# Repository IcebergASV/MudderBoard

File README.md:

# MudderBoard
KiCad Development of the 2024-2025 PCB; The MudderBoard

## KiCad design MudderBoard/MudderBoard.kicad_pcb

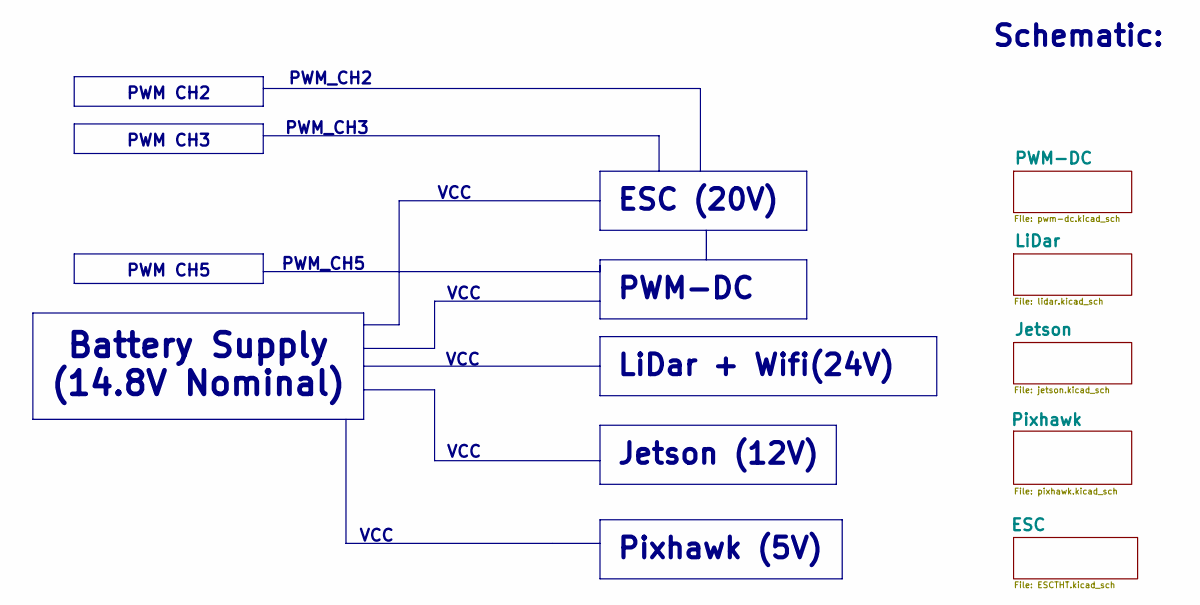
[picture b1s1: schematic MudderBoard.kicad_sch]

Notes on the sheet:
PWM CH2
PWM CH5
Pixhawk (5V)
Jetson (12V)
LiDar + Wifi(24V)
PWM-DC
ESC (20V)
Battery Supply (14.8V Nominal)
PWM CH3
VCC
PWM_CH3
PWM_CH2
PWM_CH5
Schematic:

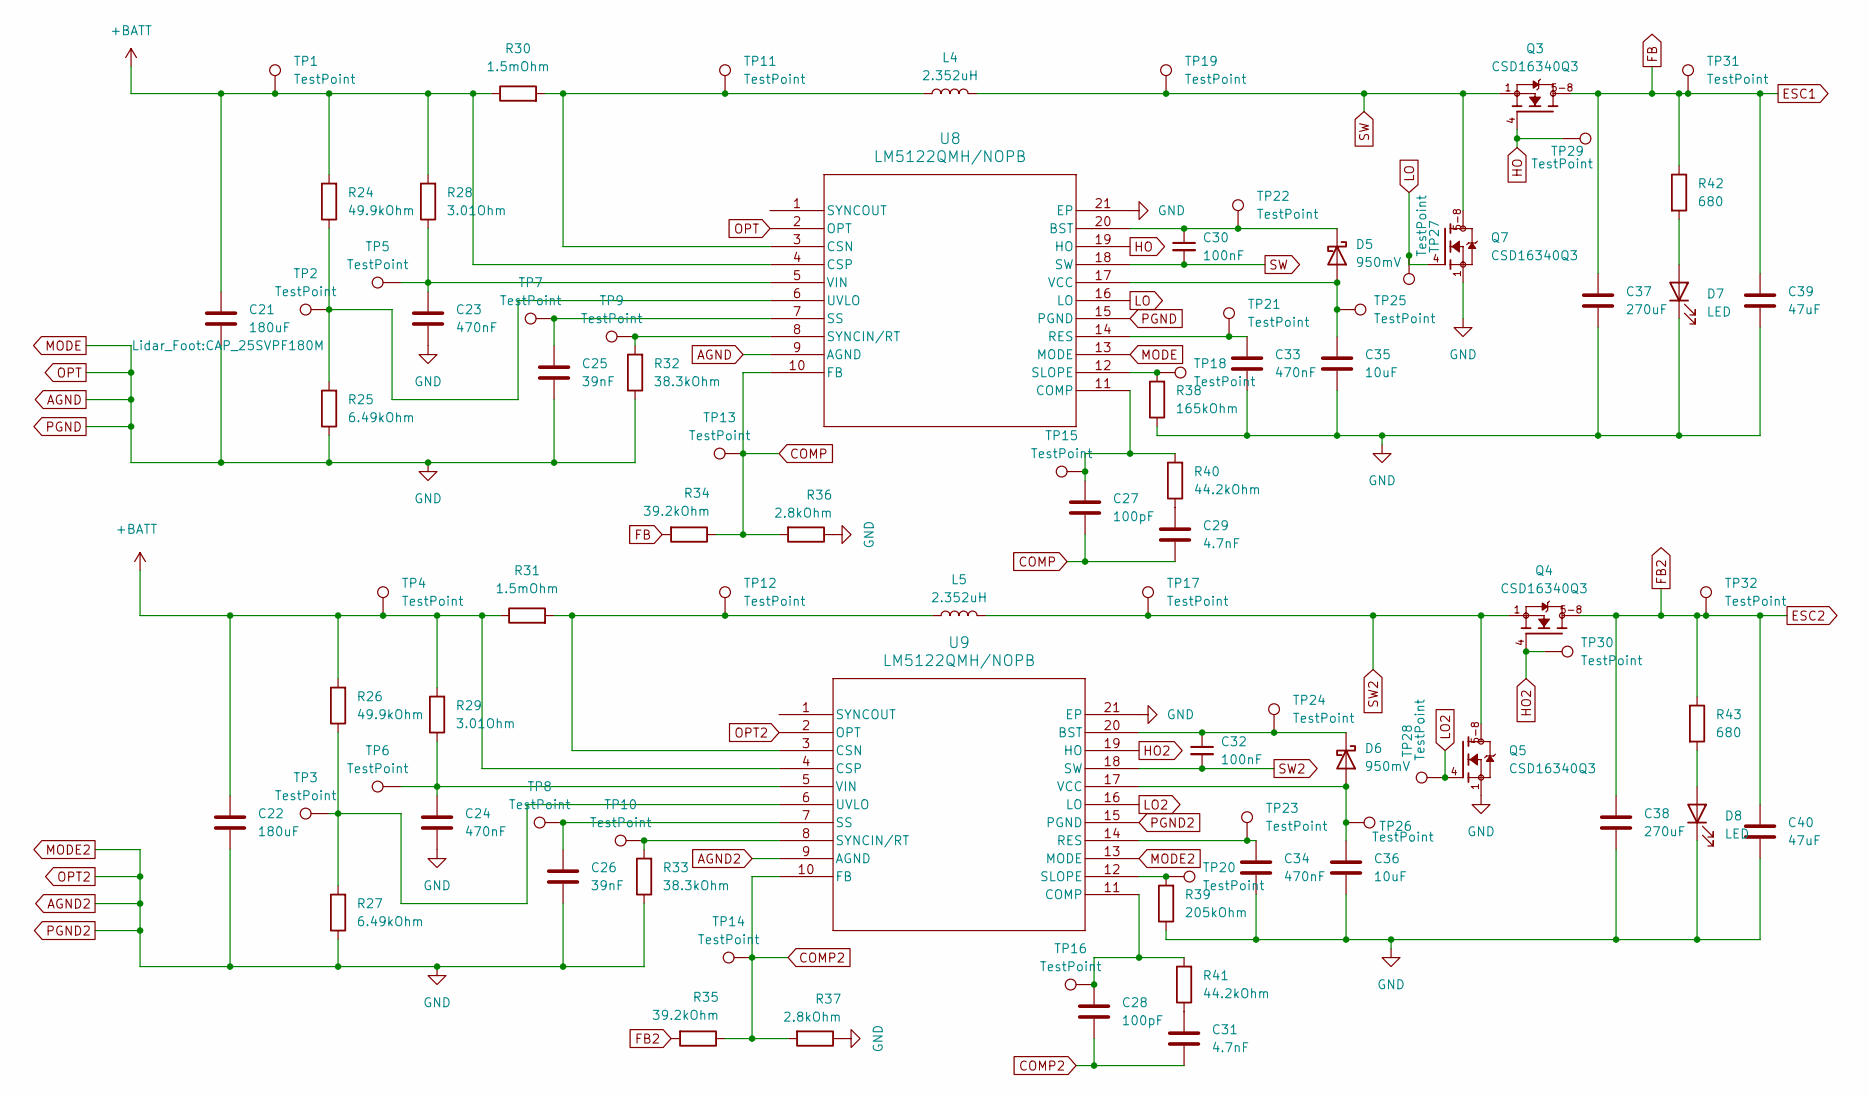
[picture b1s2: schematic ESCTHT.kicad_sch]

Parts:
C21, C22: 180uF; CAP_25SVPF180M
C23, C24: 470nF; CAPC1608X90N
C25, C26: 39nF; CAPC1005X55N
C27, C28: 100pF; CAPC2012X135N
C29, C31: 4.7nF; CAPC2012X75N
C30, C32: 100nF; CAP_CC0805_YAG
C33, C34: 470nF; CAPC2012X95N
C35, C36: 10uF; CAPC2012X135N
C37, C38: 270uF; CAP_EEHZA1V271P
C39, C40: 47uF; CAPC3216X180N
D5, D6: 950mV; CR_DO-214ACSMA_TWS
D7, D8: LED; LED_DRD1204W-TR
L4, L5: 2.352uH; L_Neosid_SM-PIC0512H
Q3, Q4, Q5, Q7: CSD16340Q3; TRANS_CSD16340Q3; PARTREV E
R24, R26: 49.9kOhm; RESC1005X40N
R25, R27: 6.49kOhm; RESC1005X40N
R28, R29: 3.01Ohm; RESC1005X40N
R30, R31: 1.5mOhm; RESC6432X110N
R32, R33: 38.3kOhm; RESC1005X40N
R34, R35: 39.2kOhm; RESC1005X35N
R36, R37: 2.8kOhm; RESC1005X40N
R38: 165kOhm; RESC1005X40N
R39: 205kOhm; RESC1005X40N
R40, R41: 44.2kOhm; RESC0603X28N
R42, R43: 680; RESC3216X70N
TP1, TP2, TP3, TP4, TP5, TP6, TP7, TP8, TP9, TP10, TP11, TP12, TP13, TP14, TP15, TP16, TP17, TP18, TP19, TP20, TP21, TP22, TP23, TP24, TP25, TP26, TP27, TP28, TP29, TP30, TP31, TP32: TestPoint; TestPoint_Keystone_5000-5004_Miniature
U8, U9: LM5122QMH/NOPB; SOP65P640X110-21N

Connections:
+BATT: C21.1, C22.1, R24.2, R26.2, R28.2, R29.2, R30.1, R31.1, TP1.1, TP4.1, U8.4 (CSP), U9.4 (CSP); also elsewhere on the board
AGND: C21.2, C22.2, C23.2, C24.2, C25.2, C26.2, C33.2, C34.2, C35.2, C36.2, C37.2, C38.2, C39.2, C40.2, D7.1 (K), D8.1 (K), Q5.1, Q5.2, Q5.3, Q7.1, R25.1, R27.1, R32.1, R33.1, R36.1, R37.1, R38.1, R39.1, U8.2 (OPT), U8.9 (AGND), U8.13 (MODE), U8.15 (PGND), U8.21 (EP), U9.2 (OPT), U9.9 (AGND), U9.13 (MODE), U9.15 (PGND), U9.21 (EP); also elsewhere on the board
COMP: C27.2, C29.2, R34.1, R36.2, TP13.1, U8.10 (FB)
COMP2: C28.2, C31.2, R35.1, R37.2, TP14.1, U9.10 (FB)
ESC1: C37.1, C39.1, Q3.5-8, R34.2, R42.1, TP31.1
ESC2: C38.1, C40.1, Q4.5-8, R35.2, R43.1, TP32.1
HO: Q3.4, TP29.1, U8.19 (HO)
HO2: Q4.4, TP30.1, U9.19 (HO)
LO: Q7.4, TP27.1, U8.16 (LO)
LO2: Q5.4, TP28.1, U9.16 (LO); also elsewhere on the board
unnamed: C29.1, R40.1
unnamed: C31.1, R41.1
unnamed: C35.1, D5.2 (A), TP25.1, U8.17 (VCC)
unnamed: C30.1, D5.1 (K), TP22.1, U8.20 (BST)
unnamed: C36.1, D6.2 (A), TP26.1, U9.17 (VCC)
unnamed: C32.1, D6.1 (K), TP24.1, U9.20 (BST)
unnamed: D7.2 (A), R42.2
unnamed: D8.2 (A), R43.2
unnamed: C27.1, R40.2, TP15.1, U8.11 (COMP)
unnamed: L4.1, R30.2, TP11.1, U8.3 (CSN)
unnamed: C33.1, TP21.1, U8.14 (RES)
unnamed: R38.2, TP18.1, U8.12 (SLOPE)
unnamed: C25.1, TP7.1, U8.7 (SS)
unnamed: R32.2, TP9.1, U8.8 (SYNCIN/RT)
unnamed: R24.1, R25.2, TP2.1, U8.6 (UVLO)
unnamed: C23.1, R28.1, TP5.1, U8.5 (VIN)
unnamed: C28.1, R41.2, TP16.1, U9.11 (COMP)
unnamed: L5.1, R31.2, TP12.1, U9.3 (CSN)
unnamed: C34.1, TP23.1, U9.14 (RES)
unnamed: R39.2, TP20.1, U9.12 (SLOPE)
unnamed: C26.1, TP8.1, U9.7 (SS)
unnamed: R33.2, TP10.1, U9.8 (SYNCIN/RT)
unnamed: R26.1, R27.2, TP3.1, U9.6 (UVLO)
unnamed: C24.1, R29.1, TP6.1, U9.5 (VIN)
SW: C30.2, L4.2, Q3.1, Q7.5-8, TP19.1, U8.18 (SW)
SW2: C32.2, L5.2, Q4.1, Q4.2, Q4.3, Q5.5-8, TP17.1, U9.18 (SW)

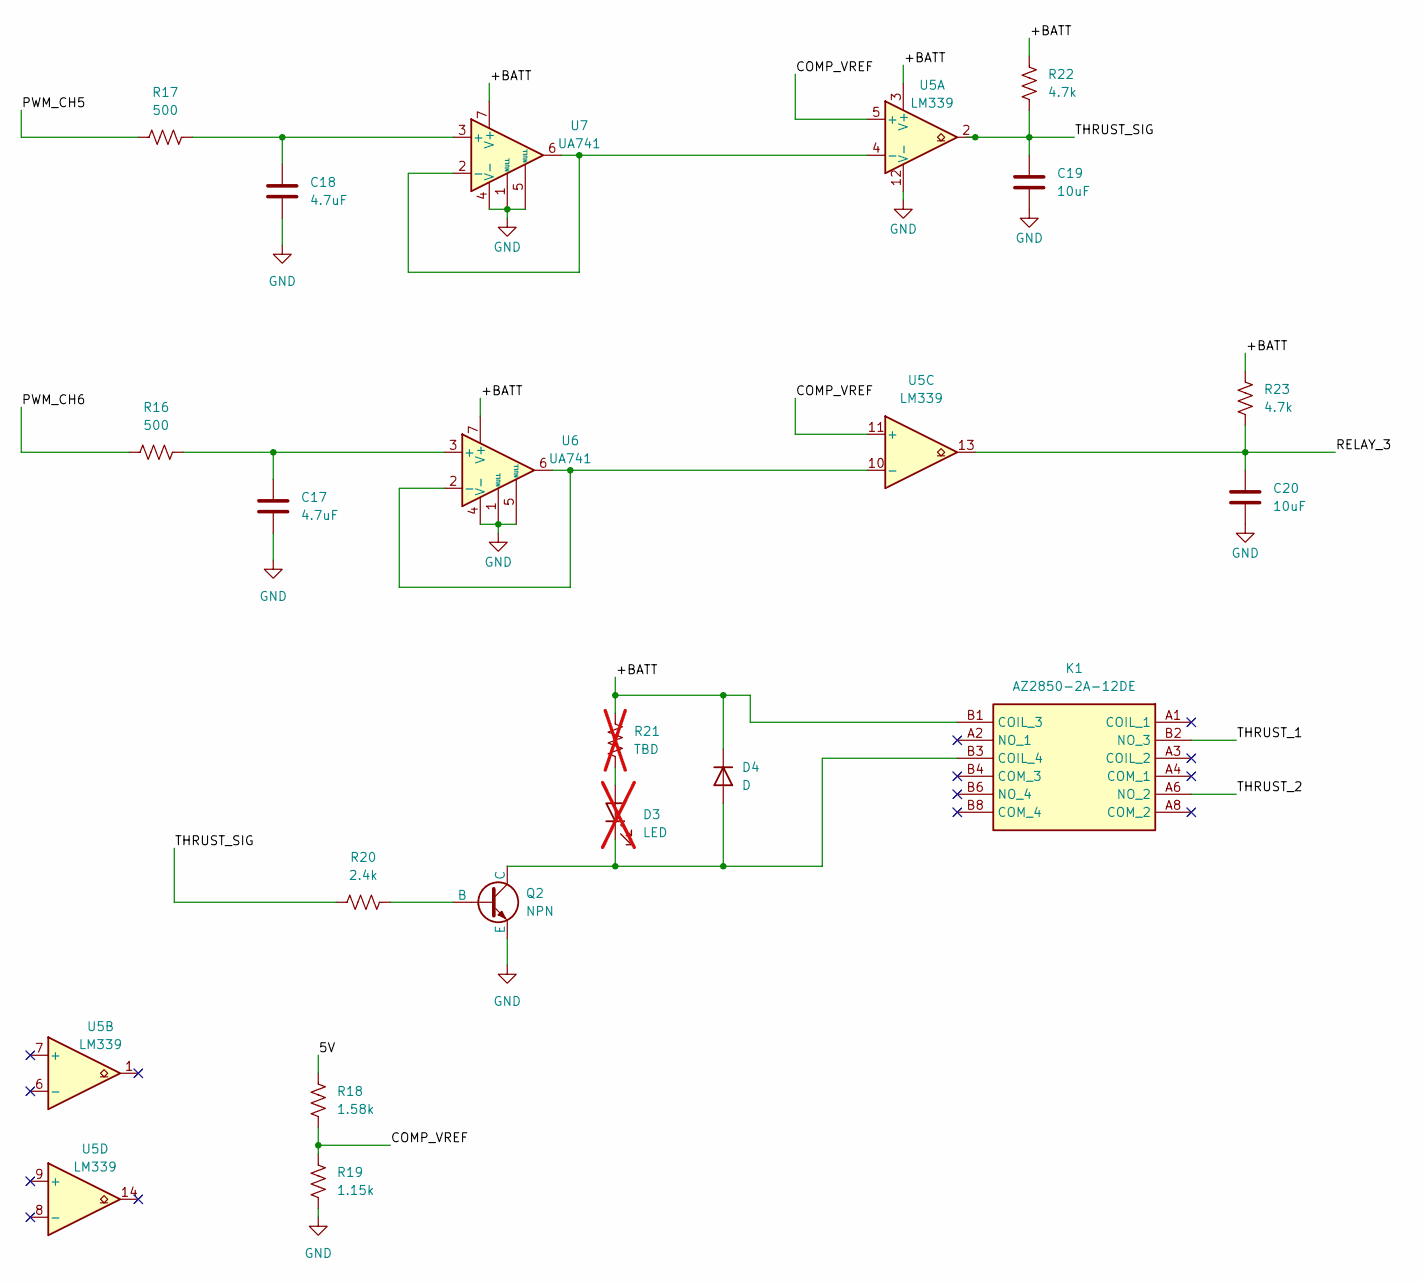
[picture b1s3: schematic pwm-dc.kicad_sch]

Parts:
C17, C18: 4.7uF; CAPC2012X140N
C19, C20: 10uF; CAPC2012X135N
D3: LED; not fitted
D4: D; SOT_45-M3&slash_I_VIS
K1: AZ2850-2A-12DE; AZ28502A12DE; Manufacturer_Part_Number AZ2850-2A-12DE
Q2: NPN; SOT95P237X111-3N
R16, R17: 500; RESC1608X55N
R18: 1.58k; RES_ERA6AEB1581V
R19: 1.15k; RES_ERA6AEB1581V
R20: 2.4k; RESC1607X60N
R21: TBD; not fitted
R22, R23: 4.7k; RESC2012X65N
U5: LM339; TSSOP-14_4.4x5mm_P0.65mm
U6, U7: UA741; SOIC127P599X175-8N

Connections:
/PWM-DC/5V: R18.2
/PWM-DC/+BATT: D4.1 (K), K1.B1 (COIL_3), R21.2, R22.2, R23.2, U5.3 (V+), U6.7 (V+), U7.7 (V+)
/PWM-DC/COMP_VREF: R18.1, R19.2, U5.5 (+), U5.11 (+)
/PWM-DC/PWM_CH5: R17.1
/PWM-DC/PWM_CH6: R16.1
/PWM-DC/RELAY_3: C20.1, R23.1, U5.13
/PWM-DC/THRUST_1: K1.B2 (NO_3)
/PWM-DC/THRUST_2: K1.A6 (NO_2)
/PWM-DC/THRUST_SIG: C19.2, R20.1, R22.1, U5.2
AGND: C17.2, C18.2, C19.1, C20.2, Q2.3 (E), R19.1, U5.12 (V-), U6.1 (NULL), U6.4 (V-), U6.5 (NULL), U7.1 (NULL), U7.4 (V-), U7.5 (NULL); also elsewhere on the board
unnamed: D3.1 (K), D4.2 (A), K1.B3 (COIL_4), Q2.1 (C)
unnamed: D3.2 (A), R21.1
unnamed: Q2.2 (B), R20.2
unnamed: U5.4 (-), U7.2 (-), U7.6
unnamed: U5.10 (-), U6.2 (-), U6.6
unnamed: C17.1, R16.2, U6.3 (+)
unnamed: C18.1, R17.2, U7.3 (+)

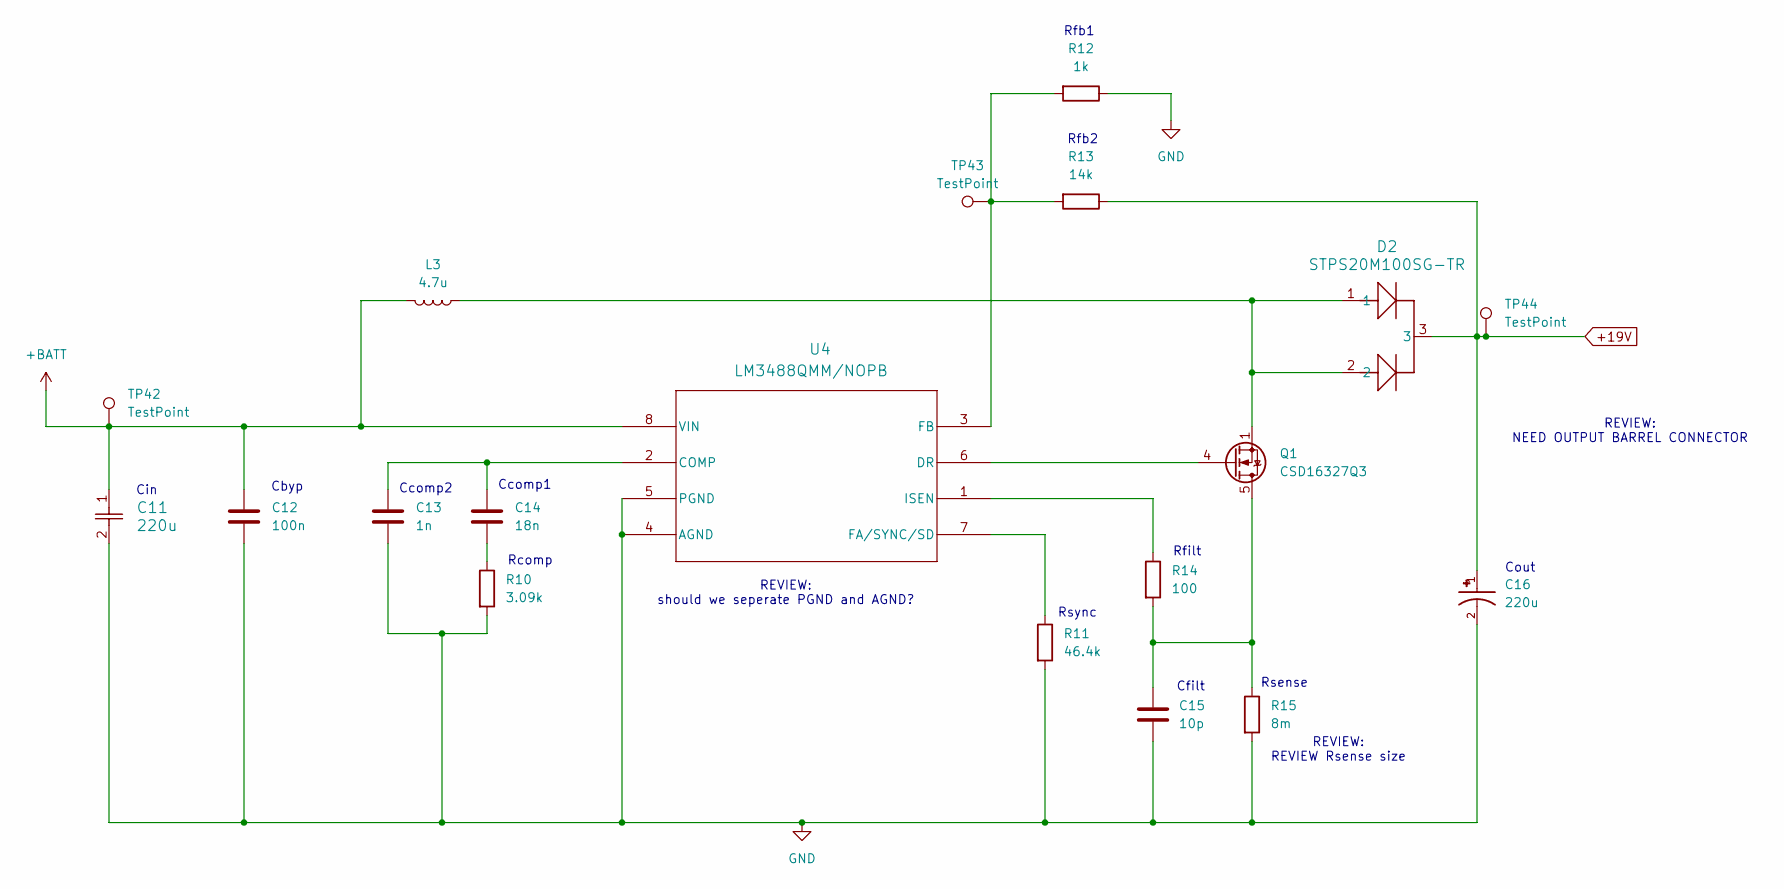
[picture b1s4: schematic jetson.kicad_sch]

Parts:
C11: 220u; U2-P_NCH
C12: 100n; C_0805_2012Metric
C13: 1n; C_0805_2012Metric
C14: 18n; C_0402_1005Metric
C15: 10p; C_0805_2012Metric
C16: 220u; CAP_35SVPF82M; PARTREV 28-Jun-19
D2: STPS20M100SG-TR; D2PAK_STM
L3: 4.7u; PA2240
Q1: CSD16327Q3; VSON-8_3.3x3.3mm_P0.65mm_NexFET
R10: 3.09k; R_0402_1005Metric
R11: 46.4k; R_0402_1005Metric
R12: 1k; R_0402_1005Metric
R13: 14k; R_0402_1005Metric
R14: 100; R_0402_1005Metric
R15: 8m; R_0603_1608Metric
TP42, TP43, TP44: TestPoint; TestPoint_Pad_1.0x1.0mm
U4: LM3488QMM/NOPB; DGK8

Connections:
+19V: C16.1, D2.3, R13.1, TP44.1
+BATT: C11.1, C12.1, L3.2, TP42.1, U4.8 (VIN); also elsewhere on the board
AGND: C11.2, C12.2, C13.2, C15.2, C16.2, R10.2, R11.2, R12.1, R15.2, U4.4 (AGND), U4.5 (PGND); also elsewhere on the board
unnamed: C14.2, R10.1
unnamed: D2.1, D2.2, L3.1, Q1.1 (S), Q1.2 (S), Q1.3 (S)
unnamed: C15.1, Q1.5 (D), R14.2, R15.1
unnamed: Q1.4 (G), U4.6 (DR)
unnamed: C13.1, C14.1, U4.2 (COMP)
unnamed: R11.1, U4.7 (FA/SYNC/SD)
unnamed: R12.2, R13.2, TP43.1, U4.3 (FB)
unnamed: R14.1, U4.1 (ISEN)

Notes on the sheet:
REVIEW: NEED OUTPUT BARREL CONNECTOR
REVIEW: should we seperate PGND and AGND?
Cfilt
Rsense
Ccomp2
REVIEW: REVIEW Rsense size
Ccomp1
Rcomp
Cin
Rfb1
Rfilt
Rfb2
Cout
Cbyp
Rsync

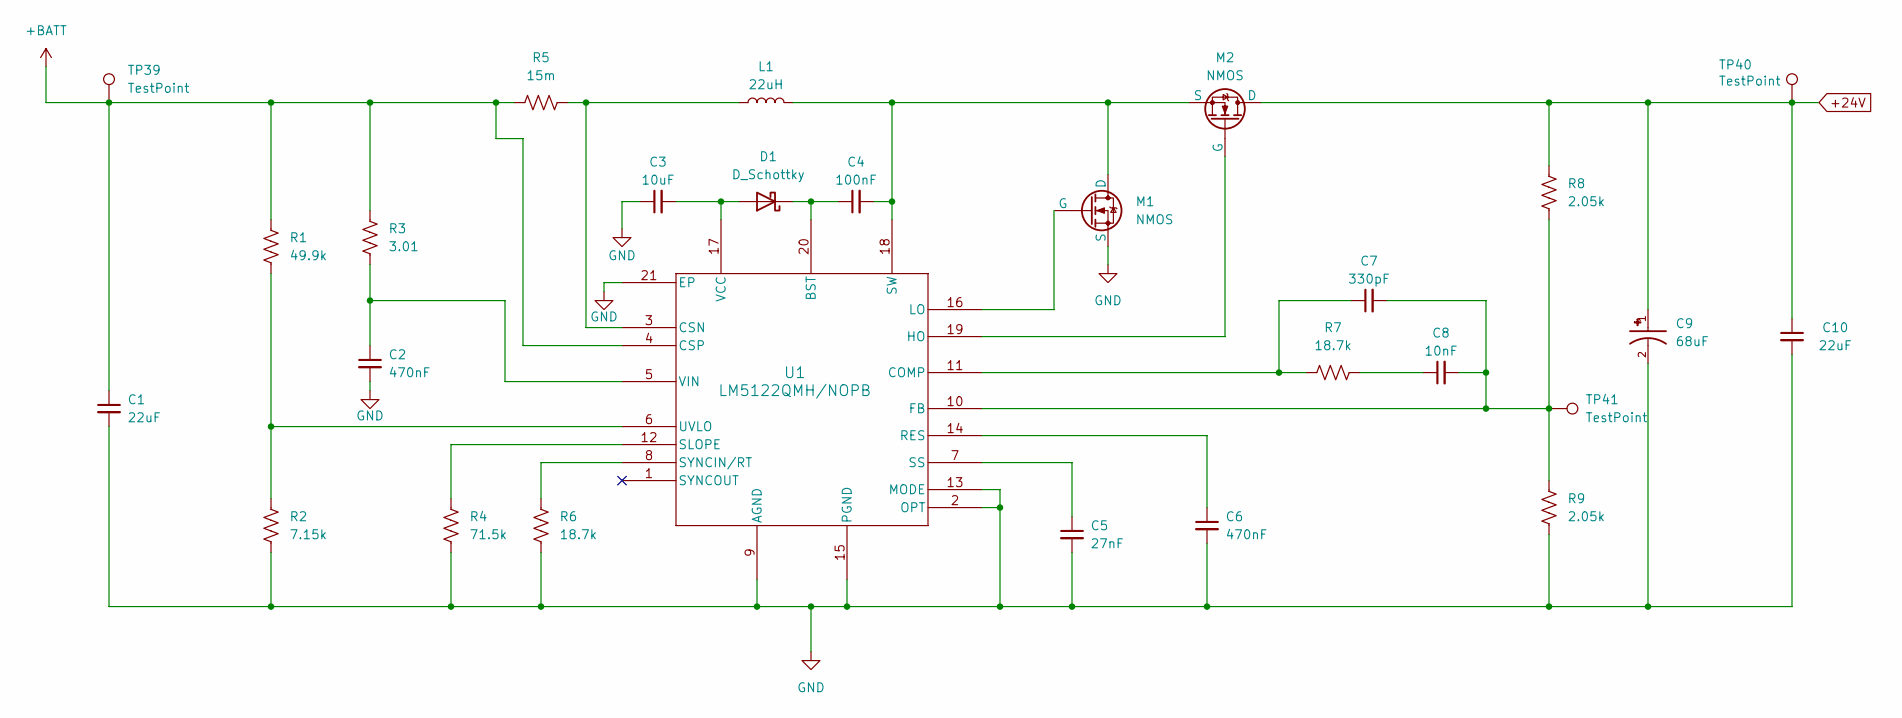
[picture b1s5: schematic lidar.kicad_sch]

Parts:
C1: 22uF; CAPC3216X180N
C2: 470nF; CAPC1608X90N
C3: 10uF; CAPC2012X135N
C4: 100nF; CAPC2012X88N
C5: 27nF; CAPC1005X55N
C6: 470nF; CAPC2012X95N
C7: 330pF; CAPC0603X33N
C8: 10nF; CAPC2012X75N
C9: 68uF; CAP_EEHZA1V680XP; PARTREV 30-Sep-20
C10: 22uF; CAPC2012X145N
D1: D_Schottky; DIOM4325X250N
L1: 22uH; IND_SRR1210-220M
M1, M2: NMOS; TRANS_CSD17571Q2
R1: 49.9k; RESC1005X40N
R2: 7.15k; RESC1005X40N
R3: 3.01; RESC1508X50N
R4: 71.5k; RESC1005X40N
R5: 15m; R_1206_3216Metric_Pad1.30x1.75mm_HandSolder
R6, R7: 18.7k; RESC0603X26N
R8: 2.05k; RESC1607X60N
R9: 2.05k; RESC1005X40N
TP39, TP40, TP41: TestPoint; TestPoint_Pad_1.0x1.0mm
U1: LM5122QMH/NOPB; SOP65P640X110-21N

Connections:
+24V: C9.1, C10.1, M2.1 (D), R8.1, TP40.1
+BATT: C1.1, R1.1, R3.1, R5.1, TP39.1, U1.4 (CSP); also elsewhere on the board
AGND: C1.2, C2.2, C3.1, C5.2, C6.2, C9.2, C10.2, M1.3 (S), R2.2, R4.2, R6.2, R9.2, U1.2 (OPT), U1.9 (AGND), U1.13 (MODE), U1.15 (PGND), U1.21 (EP); also elsewhere on the board
unnamed: C8.1, R7.1
unnamed: C3.2, D1.2 (A), U1.17 (VCC)
unnamed: C4.1, D1.1 (K), U1.20 (BST)
unnamed: C4.2, L1.2, M1.1 (D), M2.3 (S), U1.18 (SW)
unnamed: M1.2 (G), U1.16 (LO)
unnamed: M2.2 (G), U1.19 (HO)
unnamed: C7.1, R7.2, U1.11 (COMP)
unnamed: L1.1, R5.2, U1.3 (CSN)
unnamed: C7.2, C8.2, R8.2, R9.1, TP41.1, U1.10 (FB)
unnamed: C6.1, U1.14 (RES)
unnamed: R4.1, U1.12 (SLOPE)
unnamed: C5.1, U1.7 (SS)
unnamed: R6.1, U1.8 (SYNCIN/RT)
unnamed: R1.2, R2.1, U1.6 (UVLO)
unnamed: C2.1, R3.2, U1.5 (VIN)

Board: 2 copper layers, 170 parts (0 on the bottom side), 76 nets, no tracks yet.

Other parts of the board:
Cff1: 33p; CAPC1005X55N
Cin1, Cin2: 10u; CAPC2012X140N
CinLDO1: 1u; CAPC1608X90N
Cinx1: 100n; CAPC1608X90N
CoLDO1: 1u; CAPC1608X90N
Cout1, Cout2, Cout3, Cout4: 22u; CAPC2012X135N
Coutx1: 100n; CAPC1608X90N
L2: 2.2u; XAL5030222MEC
Renb1: 14k3; RESC1005X40N
Rent1: 100k; R_0402_1005Metric_Pad0.72x0.64mm_HandSolder
Rfbb1: 30k; R_0603_1608Metric_Pad0.98x0.95mm_HandSolder
Rfbt1: 220k; R_0603_1608Metric_Pad0.98x0.95mm_HandSolder
TP28#2: TestPoint; TestPoint_Keystone_5000-5004_Miniature
TP33, TP34, TP35, TP36, TP37, TP38: TestPoint; TestPoint_Pad_1.0x1.0mm
U2: TPS566242DRLR; SOT5x3_DRL_TEX
U3: LP38691DTX-3.3/NOPB; TO228P1042X238-3N

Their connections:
3V3: CoLDO1.1, TP37.1, U3.1 (Vout)
5V: Cff1.1, CinLDO1.1, Cout1.1, Cout2.1, Cout3.1, Cout4.1, Coutx1.1, L2.2, Rfbt1.1, TP34.1, TP36.1, U3.3 (Vin)
+BATT: Cin1.1, Cin2.1, Cinx1.1, Rent1.1, TP33.1, U2.1 (VIN); also elsewhere on the board
AGND: Cin1.2, Cin2.2, CinLDO1.2, Cinx1.2, CoLDO1.2, Cout1.2, Cout2.2, Cout3.2, Cout4.2, Coutx1.2, Renb1.2, Rfbb1.2, U2.3 (GND), U2.4 (AGND), U3.2 (GND); also elsewhere on the board
EN: Renb1.1, Rent1.2, TP38.1, U2.2 (EN)
LO2: TP28#2.1; also elsewhere on the board
unnamed: Cff1.2, Rfbb1.1, Rfbt1.2, TP35.1, U2.5 (FB)
unnamed: L2.1, U2.6 (SW)

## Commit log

2024-02-29 Title Block Editing in Schem.
2024-02-29 Title Block Update
2024-03-02 export title block
2024-03-02 Updated gitignore to ignore backups directory
2024-03-05 Ben name Added
2024-03-05 Ben name again
2024-03-05 ben again.
2024-03-05 closed
2024-03-05 Penis
2024-03-05 ben plus
2024-03-06 Circumsision
2024-03-06 woohoo
2024-03-06 Iceberg Logo
2024-03-07 showed colin repo
2024-03-16 LiDar Schematic
2024-03-17 softstart_Lidar
2024-03-18 schematic_controller update
2024-03-18 Pixhawk
    Added pixhawk project file
2024-03-18 Added Lm25117
2024-03-18 Iceberg logo on lidar page
2024-03-18 ULVO Lidar
2024-03-19 Block Diagram
2024-03-19 post meeting
2024-03-20 Component Sorting
2024-03-20 mosfet selection LiDar
2024-03-21 Lidar edits
2024-03-23 note on input cap
2024-03-24 Lidar_Sim
2024-03-30 cap switch Lidar
2024-04-14 deleted BattMon
2024-04-19 Adding LM5123 Footprint
    Added LM5123-Q1 footprint. I didn't realize Benihana already made one!
2024-04-19 ESC Schematic
    Started ESC Schematic.
2024-04-20 Added 24V Boost
2024-04-21 Working on ESC Circuit
    Still working...
2024-04-21 ESC Boost Converter Circuit
    Finished design of ESC boost converter design and added some component libraries.
2024-04-23 ESC Board Changes
2024-04-24 Combined Wifi and Lidar Pages
2024-05-03 ESC Boost Converter THT
    Designing new THT boost converter.
2024-05-04 Updating the ESC Controller
    Completed design without selecting footprints.
2024-05-04 Updated Lidar Circuit
2024-05-11 Update Pixhawk.kicad_sch
    Updated with pixhawk circuit
2024-05-12 Updated pixhawk converter
    added more decoupling caps
2024-05-12 Updated Pixhawk Buck
2024-05-12 Test?
2024-05-13 Added PWM-DC Circuit
2024-05-18 Small Updates
2024-05-18 ESC Boost Controllers
    Added test points and status LEDs.
2024-05-18 added relay driver
2024-05-22 connected relay
2024-05-27 added jetson circuit
2024-06-02 downloaded footprints for Lidar
2024-06-02 downloaded PWM-DC footprints
2024-06-08 added lidar footprints
2024-06-08 added all footprints to Jetson circuit
2024-06-08 AddedPWM-DC footprints
2024-06-15 added pixhawk footprints
2024-06-15 ESC Footprints
    Added footprints for ESC controllers. Need to add inductor and fix MOSFETS.
2024-06-17 Imported footprints to layout
    Colin - Make note of these
    C30,C32 are generic 0805 caps
    L4,L5 are basic insuctors, will need to change when we figure this situation out!
    U8,U9 changed to same boost IC as Lidar - these are the same right?
2024-06-19 prelim layout for Lidar Boost
2024-06-22 Preliminary ESC Boost Layout
    Arranged footprints and test points. Still need to route but waiting to see how many layers etc.
2024-06-23 PixHawk Layout Updates
2024-06-25 updated layout with Lidar placement
2024-06-25 updated layout with Lidar placemen
2024-06-25 revert to eli changes
2024-06-26 pixhawk
2024-06-26 edge cuts
2024-06-26 revert to colin changes
2024-06-26 erased pcb data
2024-06-26 replaced PCB file
2024-06-26 edited lidar footprints
2024-06-26 Preliminary layout for jetson portion
2024-06-27 lidar preliminary layout
2024-06-29 PWM-DC prelim layout
2024-07-02 pixhawk layout prelim
2024-07-06 test
2024-07-12 Layout
    Pixhawk and Lidar
2024-07-12 Layout
    Final save, pixhawk and lidar
2024-07-12 Schematic updates
    global labels and test points
2024-07-12 Schematic and Layout
    TPs and net labels
2024-07-17 Layout
    ESC
